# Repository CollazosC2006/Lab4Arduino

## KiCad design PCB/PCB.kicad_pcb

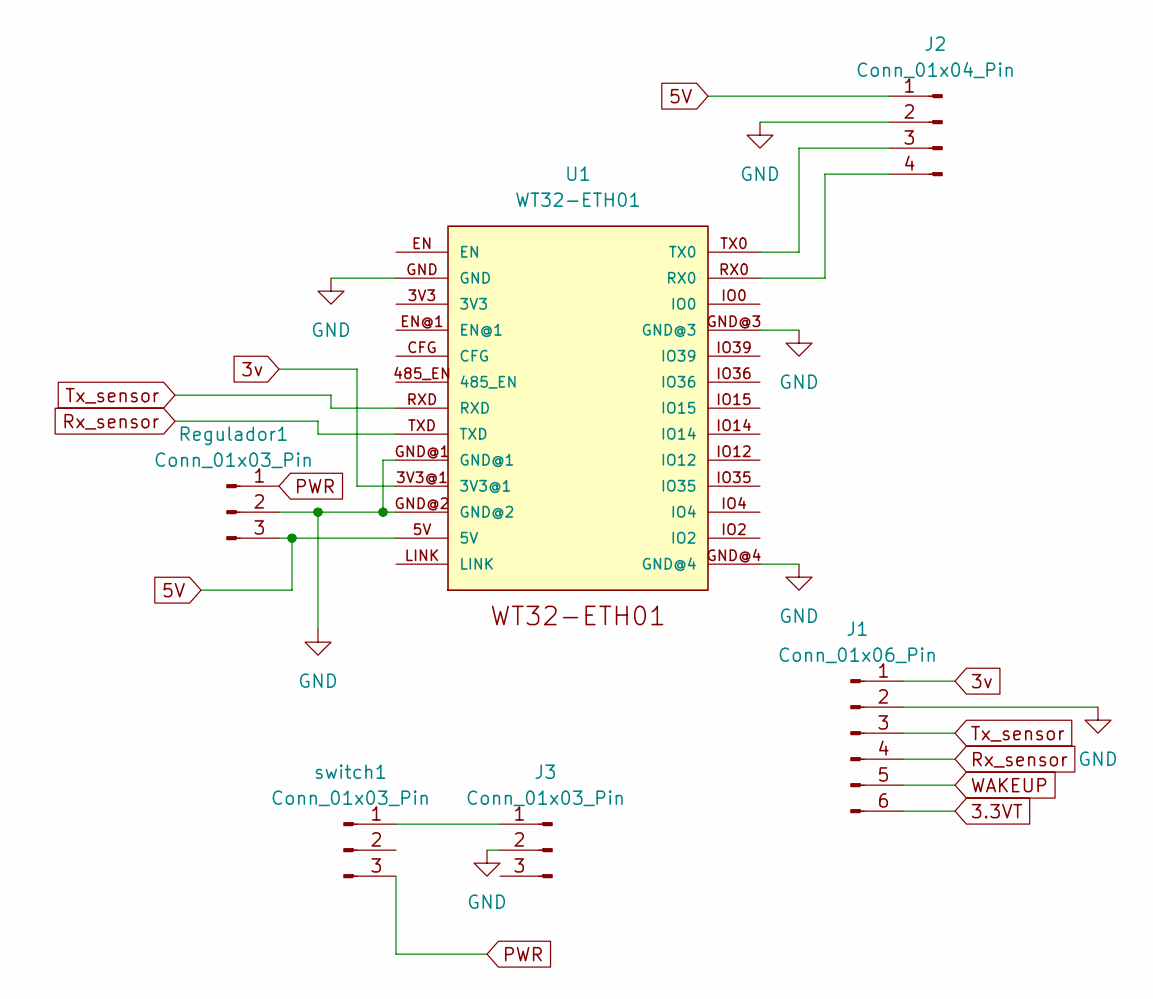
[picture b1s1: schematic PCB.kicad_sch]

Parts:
J1: Conn_01x06_Pin; Molex_KK-254_AE-6410-06A_1x06_P2.54mm_Vertical
J2: Conn_01x04_Pin; Molex_KK-254_AE-6410-04A_1x04_P2.54mm_Vertical
J3: Conn_01x03_Pin; BarrelJack_GCT_DCJ200-10-A_Horizontal
Regulador1: Conn_01x03_Pin; PinHeader_1x03_P2.54mm_Vertical
U1: WT32-ETH01
switch1: Conn_01x03_Pin; PinHeader_1x03_P2.54mm_Vertical

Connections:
3.3VT: J1.6
3v: J1.1, U1.3V3@1
5V: J2.1, Regulador1.3, U1.5V
GND: J1.2, J2.2, J3.2, Regulador1.2, U1.GND, U1.GND@1, U1.GND@2, U1.GND@3, U1.GND@4
unnamed: J2.3, U1.TX0
unnamed: J2.4, U1.RX0
unnamed: J3.1, switch1.1
PWR: Regulador1.1, switch1.3
Rx_sensor: J1.4, U1.TXD
Tx_sensor: J1.3, U1.RXD
WAKEUP: J1.5

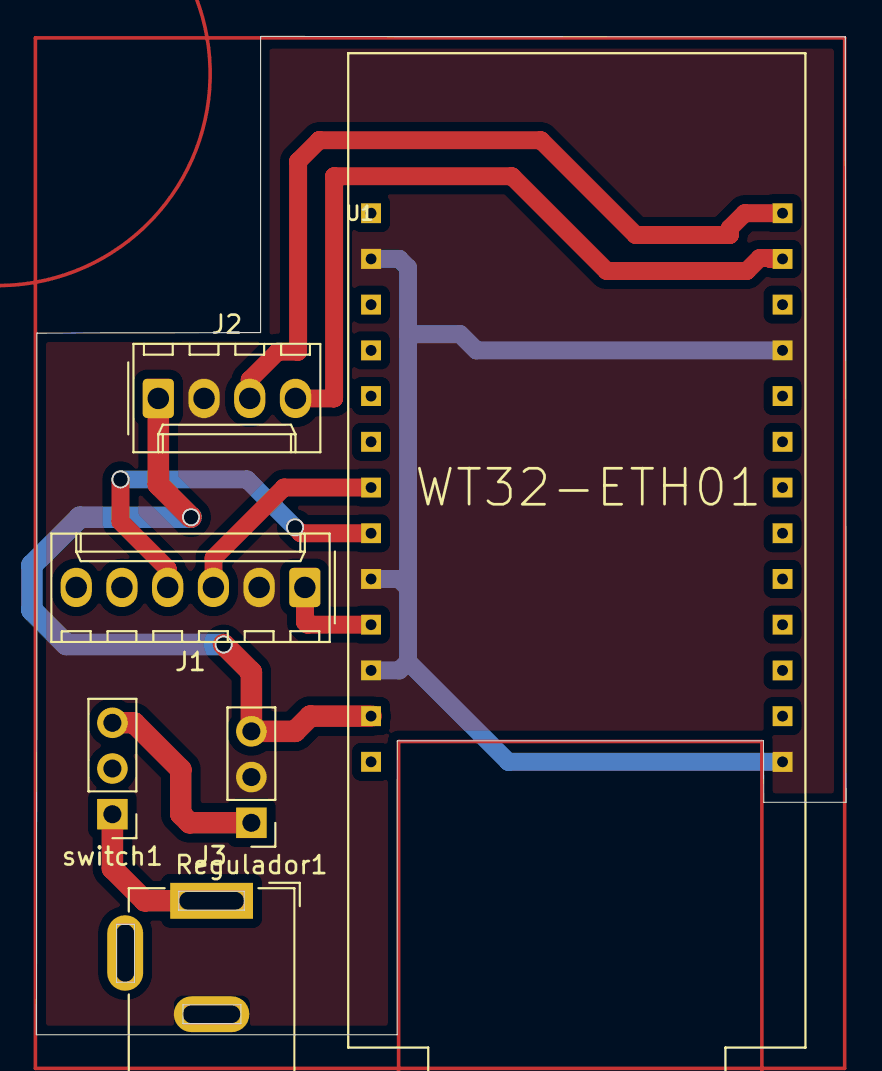
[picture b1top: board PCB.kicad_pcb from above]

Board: 2 copper layers, 45.0 x 55.5 mm, 6 parts (0 on the bottom side), 9 nets.

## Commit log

2024-11-01 data
    a
2024-11-07 hbjhb
2024-11-07 Avance en serverAutenticacion_v2
2024-11-07 Server V_2
    Registro y acceso version beta incompleta
2024-11-08 servidor_jueves
2024-11-08 Format fecha
2024-11-21 Encriptar Huellas
